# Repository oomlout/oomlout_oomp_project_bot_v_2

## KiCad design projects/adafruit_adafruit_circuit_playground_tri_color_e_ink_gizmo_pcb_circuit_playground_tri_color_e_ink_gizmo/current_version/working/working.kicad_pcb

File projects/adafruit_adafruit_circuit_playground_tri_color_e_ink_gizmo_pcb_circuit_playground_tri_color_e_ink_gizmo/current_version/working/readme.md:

# adafruit_circuit_playground_tri_color_e_ink_gizmo_pcb
 
## summary 
* id: adafruit_adafruit_circuit_playground_tri_color_e_ink_gizmo_pcb_circuit_playground_tri_color_e_ink_gizmo
* user: adafruit
* name: adafruit_circuit_playground_tri_color_e_ink_gizmo_pcb
* board: circuit_playground_tri_color_e_ink_gizmo
* repo: https://github.com/adafruit/Adafruit-Circuit-Playground-Tri-Color-E-Ink-Gizmo-PCB

* src_file_repo_sch: 
* src_file_repo_sch_link: https://github.com/adafruit/Adafruit-Circuit-Playground-Tri-Color-E-Ink-Gizmo-PCB/tree/master/
* full details link: https://github.com/oomlout/oomlout_oomp_project_bot_v_2/tree/main/projects/adafruit_adafruit_circuit_playground_tri_color_e_ink_gizmo_pcb_circuit_playground_tri_color_e_ink_gizmo/current_version/working  

## schematic  
  
[schematic (pdf)](working_schematic.pdf) 

## pcb  

[board (pdf)](working.pdf)  

## working_bom
| Id | Designator | Footprint | Quantity | Designation | Supplier and ref |  | None | 
| --- | --- | --- | --- | --- | --- | --- | --- | 
| 1 | Q5 | SOT23-3 | 1 | IRLML0100 |  |  | [''] | 
| 2 | R13,R12 | 0603-NO | 2 | 100 |  |  | [''] | 
| 3 | U$7 | PCBFEAT-REV-040 | 1 |  |  |  | [''] | 
| 4 | D1,D2 | SOD-323 | 2 | 3.6V |  |  | [''] | 
| 5 | C9,C13,C24,C16 | 0805-NO | 4 | 1uF |  |  | [''] | 
| 6 | TP2,TP4,TP6,TP8,TP7,TP11,TP5,TP13,TP3,TP9,TP10,TP12 | SMT_NUT_3MM | 12 | SEWTAP_SMTNUTM3 |  |  | [''] | 
| 7 | U$2,U$6,U$3 | FIDUCIAL_1MM | 3 | FIDUCIAL_1MM |  |  | [''] | 
| 8 | LEFT0,RIGHT0 | JSTPH3 | 2 | JST PH 3 |  |  | [''] | 
| 9 | C23,C22,C6,C7 | 0805-NO | 4 | 1uF/25V |  |  | [''] | 
| 10 | C8 | 0805-NO | 1 | 10uF/25V |  |  | [''] | 
| 11 | R7 | 0603-NO | 1 | 100K |  |  | [''] | 
| 12 | C10,C5 | 0805-NO | 2 | 1uF/10V |  |  | [''] | 
| 13 | C15,C1,C2 | 0805-NO | 3 | 10uF |  |  | [''] | 
| 14 | VR2 | TRIMPOT_BOURNS_3303W | 1 | 10K trim |  |  | [''] | 
| 15 | C3 | 0805-NO | 1 | 10uF/10V+ |  |  | [''] | 
| 16 | R2,R5 | 0603-NO | 2 | 1K |  |  | [''] | 
| 17 | U$1 | 53398-0271 | 1 | CON_MOLEX_2P |  |  | [''] | 
| 18 | R6 | 0805_10MGAP | 1 | .47ohm |  |  | [''] | 
| 19 | D3,D5,D4 | SOD-123 | 3 | MBR0530 |  |  | [''] | 
| 20 | L1 | INDUCTOR_4X4MM_NR401 | 1 | 10uH |  |  | [''] | 
| 21 | BUSY0 | TP15SQ | 1 | TPTP15SQ |  |  | [''] | 
| 22 | U5 | MSOP8_0.65MM | 1 | PAM8302AASCR |  |  | [''] | 
| 23 | U$4 | EINKGIZMO_BACK | 1 |  |  |  | [''] | 
| 24 | TP18,TP14,TP17,TP16,TP15,TP1 | TESTPOINT_ROUND_1.5MM_NO | 6 |  |  |  | [''] | 
| 25 | U$8 | EINKGIZMO_FRONT | 1 |  |  |  | [''] | 
| 26 | EINK2 | EINK_154IN | 1 | EINK_24PIN_154IN |  |  | [''] | 

## bom_schematic
| Ref | Qnty | Value | Cmp name | Footprint | Description | Vendor | DNP | 
| --- | --- | --- | --- | --- | --- | --- | --- | 
| BUSY0 | 1 | TPTP15SQ | TPTP15SQ | working:TP15SQ |  |  |  | 
| C1, C2, C15 | 3 | 10uF | CAP_CERAMIC0805-NOOUTLINE | working:0805-NO |  |  |  | 
| C3 | 1 | 10uF/10V+ | CAP_CERAMIC0805-NOOUTLINE | working:0805-NO |  |  |  | 
| C5, C10 | 2 | 1uF/10V | CAP_CERAMIC0805-NOOUTLINE | working:0805-NO |  |  |  | 
| C6, C7, C22, C23 | 4 | 1uF/25V | CAP_CERAMIC0805-NOOUTLINE | working:0805-NO |  |  |  | 
| C8 | 1 | 10uF/25V | CAP_CERAMIC0805-NOOUTLINE | working:0805-NO |  |  |  | 
| C9, C13, C16, C24 | 4 | 1uF | CAP_CERAMIC0805-NOOUTLINE | working:0805-NO |  |  |  | 
| D1, D2 | 2 | 3.6V | DIODE-ZENERSOD323 | working:SOD-323 |  |  |  | 
| D3, D4, D5 | 3 | MBR0530 | DIODE-SCHOTTKYSOD-123 | working:SOD-123 |  |  |  | 
| EINK2 | 1 | EINK_24PIN_154IN | EINK_24PIN_154IN | working:EINK_154IN |  |  |  | 
| L1 | 1 | 10uH | INDUCTORNR401 | working:INDUCTOR_4X4MM_NR401 |  |  |  | 
| LEFT0 | 1 | JST PH 3 | CON_JST_PH_3PIN | working:JSTPH3 |  |  |  | 
| Q5 | 1 | IRLML2060TRPBF | IRLML2060TRPBF | working:SOT23-3 |  |  |  | 
| R2, R5 | 2 | 1K | RESISTOR_0603_NOOUT | working:0603-NO |  |  |  | 
| R6 | 1 | .47ohm | RESISTOR0805_10MGAP | working:0805_10MGAP |  |  |  | 
| R7 | 1 | 100K | RESISTOR_0603_NOOUT | working:0603-NO |  |  |  | 
| R12, R13 | 2 | 100 | RESISTOR_0603_NOOUT | working:0603-NO |  |  |  | 
| RIGHT0 | 1 | JST PH 3 | CON_JST_PH_3PIN | working:JSTPH3 |  |  |  | 
| TP1, TP14, TP15, TP16, TP17, TP18 | 6 | TESTPOINTROUND1.5MMNO | TESTPOINTROUND1.5MMNO | working:TESTPOINT_ROUND_1.5MM_NO |  |  |  | 
| TP2, TP3, TP4, TP5, TP6, TP7, TP8, TP9, TP10, TP11, TP12, TP13 | 12 | SEWTAP_SMTNUTM3 | SEWTAP_SMTNUTM3 | working:SMT_NUT_3MM |  |  |  | 
| U5 | 1 | PAM8302AASCR | AUDIOAMP_PAM8302A | working:MSOP8_0.65MM |  |  |  | 
| U$1 | 1 | CON_MOLEX_2P | CON_MOLEX_2P | working:53398-0271 |  |  |  | 
| U$2, U$3, U$6 | 3 | FIDUCIAL_1MM | FIDUCIAL_1MM | working:FIDUCIAL_1MM |  |  |  | 
| VR2 | 1 | 10K trim | TRIMPOT3303W/X | working:TRIMPOT_BOURNS_3303W |  |  |  |

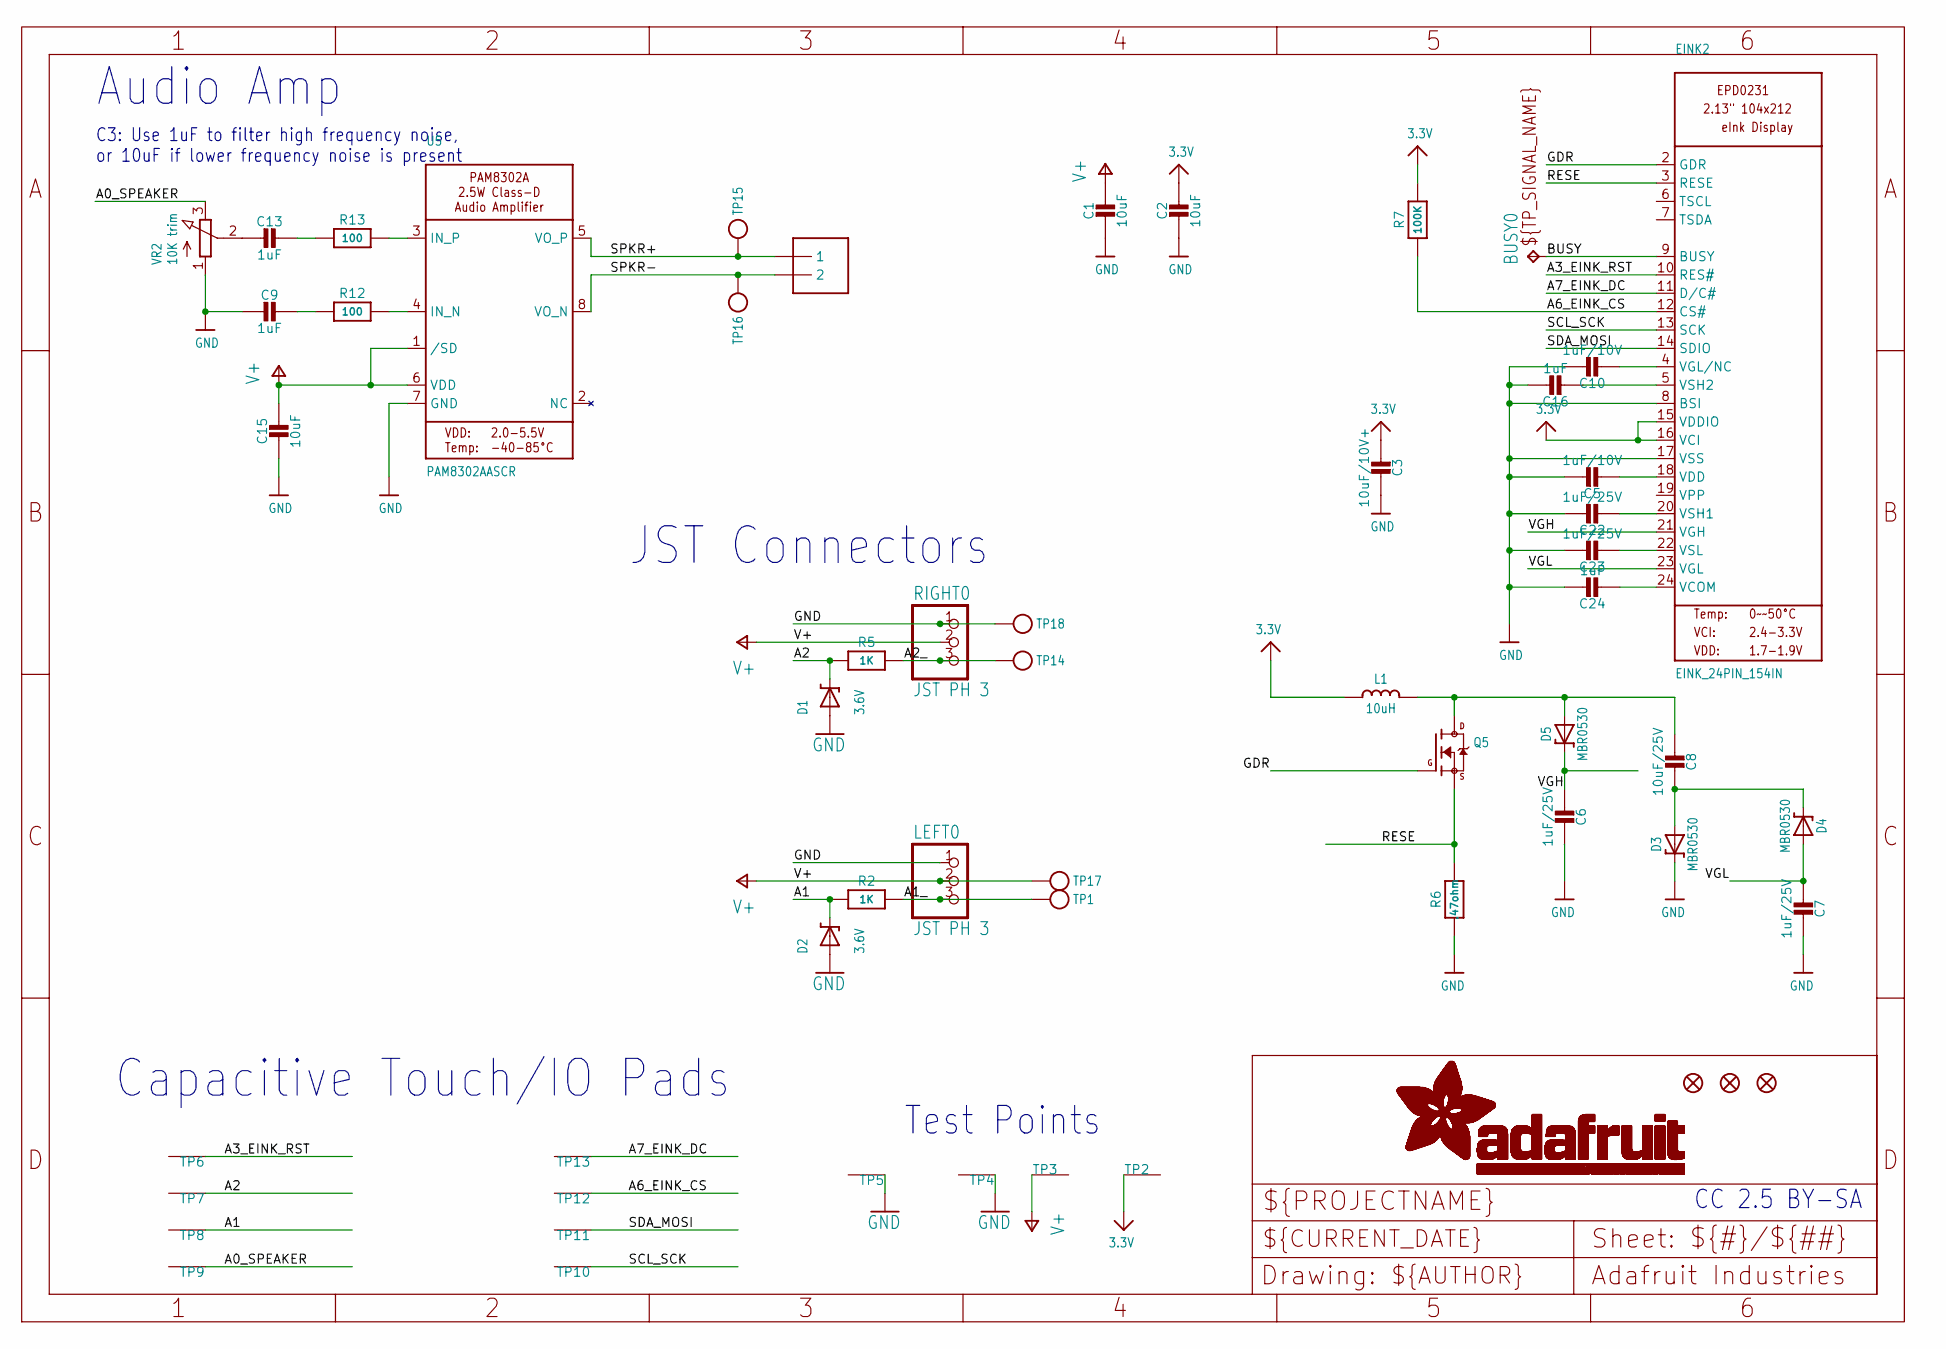
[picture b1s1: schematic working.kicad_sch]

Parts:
BUSY0: TPTP15SQ; TP15SQ
C1, C2, C15: 10uF; 0805-NO
C3: 10uF/10V+; 0805-NO
C5, C10: 1uF/10V; 0805-NO
C6, C7, C22, C23: 1uF/25V; 0805-NO
C8: 10uF/25V; 0805-NO
C9, C13, C16, C24: 1uF; 0805-NO
D1, D2: 3.6V; SOD-323
D3, D4, D5: MBR0530; SOD-123
EINK2: EINK_24PIN_154IN; EINK_154IN
L1: 10uH; INDUCTOR_4X4MM_NR401
LEFT0: JST PH 3; JSTPH3
Q5: IRLML2060TRPBF; SOT23-3
R2, R5: 1K; 0603-NO
R6: .47ohm; 0805_10MGAP
R7: 100K; 0603-NO
R12, R13: 100; 0603-NO
RIGHT0: JST PH 3; JSTPH3
TP1, TP14, TP15, TP16, TP17, TP18: TESTPOINTROUND1.5MMNO; TESTPOINT_ROUND_1.5MM_NO
TP2, TP3, TP4, TP5, TP6, TP7, TP8, TP9, TP10, TP11, TP12, TP13: SEWTAP_SMTNUTM3; SMT_NUT_3MM
U5: PAM8302AASCR; MSOP8_0.65MM
U$1: CON_MOLEX_2P; 53398-0271
U$2, U$3, U$6: FIDUCIAL_1MM
VR2: 10K trim; TRIMPOT_BOURNS_3303W

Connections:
3.3V: C2.1, C3.2, EINK2.15 (VDDIO), EINK2.16 (VCI), L1.P$2 (2), R7.2, TP2.P$1
A0_SPEAKER: TP9.P$1, VR2.3 (E)
A1: D2.C, R2.2, TP8.P$1
A1_: LEFT0.3, R2.1, TP1.P$1
A2: D1.C, R5.2, TP7.P$1
A2_: R5.1, RIGHT0.3, TP14.P$1
A3_EINK_RST: EINK2.10 (RES#), TP6.P$1
A6_EINK_CS: EINK2.12 (CS#), R7.1, TP12.P$1
A7_EINK_DC: EINK2.11 (D/C#), TP13.P$1
BUSY: BUSY0.TP, EINK2.9 (BUSY)
GDR: EINK2.2 (GDR), Q5.1 (G)
GND: C1.2, C2.2, C3.1, C5.1, C6.2, C7.2, C9.2, C10.1, C15.2, C16.1, C22.1, C23.1, C24.1, D1.A, D2.A, D3.C, EINK2.8 (BSI), EINK2.17 (VSS), LEFT0.1, R6.2, RIGHT0.1, TP4.P$1, TP5.P$1, TP18.P$1, U5.7 (GND), VR2.1 (A)
unnamed: C8.2, D3.A, D4.C
unnamed: C8.1, D5.A, L1.P$1 (1), Q5.3 (D)
unnamed: C16.2, EINK2.5 (VSH2)
unnamed: C5.2, EINK2.18 (VDD)
unnamed: C22.2, EINK2.20 (VSH1)
unnamed: C10.2, EINK2.4 (VGL/NC)
unnamed: R12.2, U5.4 (IN_N)
unnamed: R13.2, U5.3 (IN_P)
unnamed: C9.1, R12.1
unnamed: C13.1, R13.1
unnamed: C13.2, VR2.2 (S)
unnamed: C23.2, EINK2.22 (VSL)
unnamed: C24.2, EINK2.24 (VCOM)
RESE: EINK2.3 (RESE), Q5.2 (S), R6.1
SCL_SCK: EINK2.13 (SCK), TP10.P$1
SDA_MOSI: EINK2.14 (SDIO), TP11.P$1
SPKR+: TP15.P$1, U5.5 (VO_P), U$1.1
SPKR-: TP16.P$1, U5.8 (VO_N), U$1.2
V+: C1.1, C15.1, LEFT0.2, RIGHT0.2, TP3.P$1, TP17.P$1, U5.1 (/SD), U5.6 (VDD)
VGH: C6.1, D5.C, EINK2.21 (VGH)
VGL: C7.1, D4.A, EINK2.23 (VGL)

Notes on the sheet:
Audio Amp
Capacitive Touch/IO Pads
CC 2.5 BY-SA
Test Points
JST Connectors
C3: Use 1uF to filter high frequency noise, or 10uF if lower frequency noise is present

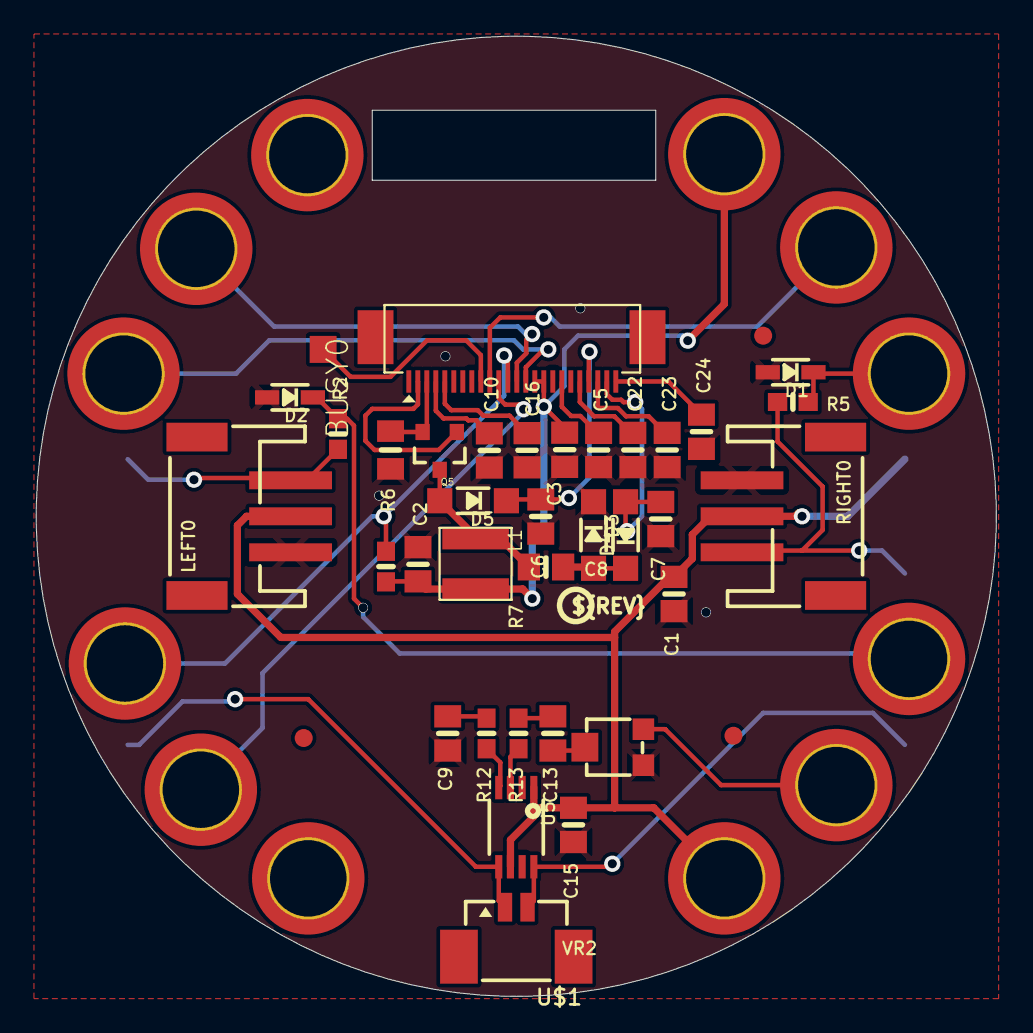
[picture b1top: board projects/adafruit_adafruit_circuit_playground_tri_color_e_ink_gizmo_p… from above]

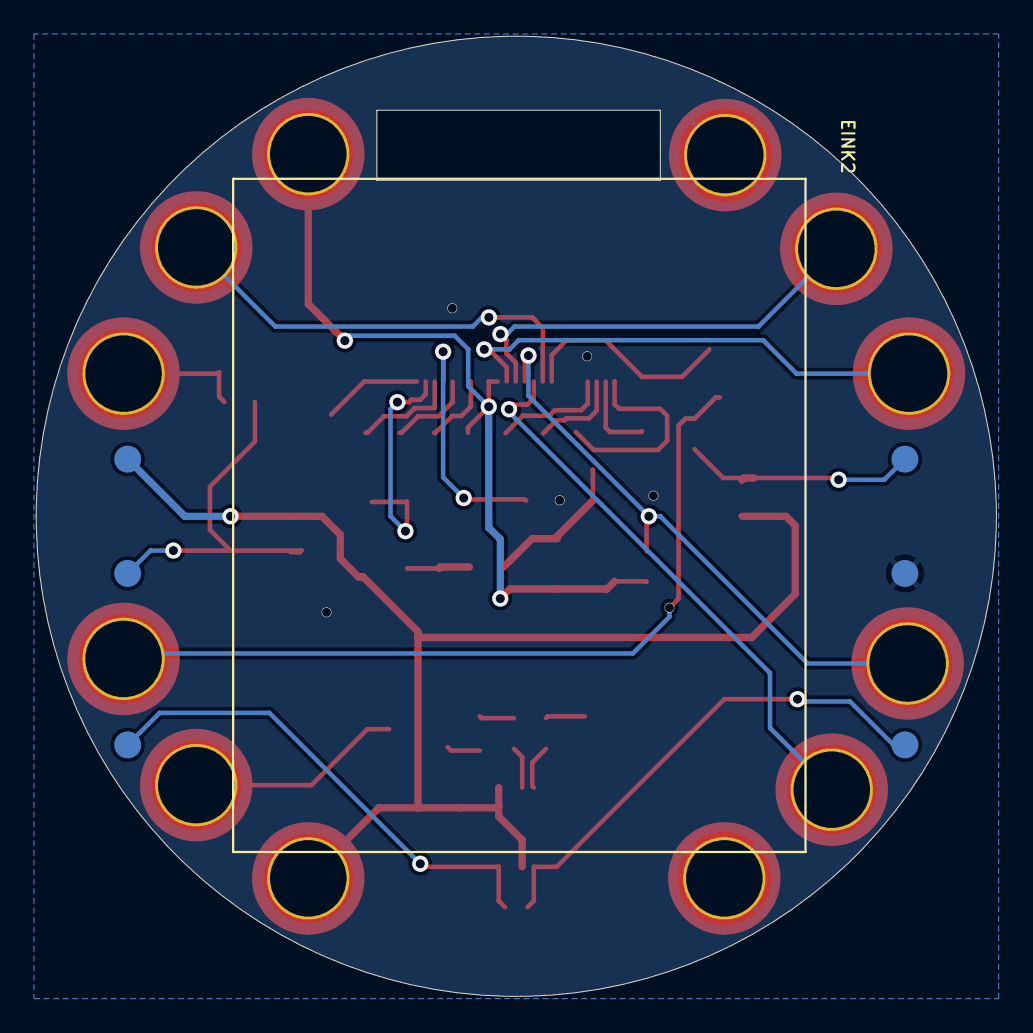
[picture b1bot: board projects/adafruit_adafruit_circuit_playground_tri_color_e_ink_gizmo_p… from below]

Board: 16 copper layers, 53.3 x 53.3 mm, 59 parts (8 on the bottom side), 33 nets.

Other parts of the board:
U$4: EINKGIZMO_BACK
U$7: PCBFEAT-REV-040
U$8: EINKGIZMO_FRONT

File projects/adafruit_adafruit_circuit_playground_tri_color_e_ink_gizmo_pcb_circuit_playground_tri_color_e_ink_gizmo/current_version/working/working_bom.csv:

"Id";"Designator";"Footprint";"Quantity";"Designation";"Supplier and ref";
1;"Q5";"SOT23-3";1;"IRLML0100";;;
2;"R13,R12";"0603-NO";2;"100";;;
3;"U$7";"PCBFEAT-REV-040";1;"";;;
4;"D1,D2";"SOD-323";2;"3.6V";;;
5;"C9,C13,C24,C16";"0805-NO";4;"1uF";;;
6;"TP2,TP4,TP6,TP8,TP7,TP11,TP5,TP13,TP3,TP9,TP10,TP12";"SMT_NUT_3MM";12;"SEWTAP_SMTNUTM3";;;
7;"U$2,U$6,U$3";"FIDUCIAL_1MM";3;"FIDUCIAL_1MM";;;
8;"LEFT0,RIGHT0";"JSTPH3";2;"JST PH 3";;;
9;"C23,C22,C6,C7";"0805-NO";4;"1uF/25V";;;
10;"C8";"0805-NO";1;"10uF/25V";;;
11;"R7";"0603-NO";1;"100K";;;
12;"C10,C5";"0805-NO";2;"1uF/10V";;;
13;"C15,C1,C2";"0805-NO";3;"10uF";;;
14;"VR2";"TRIMPOT_BOURNS_3303W";1;"10K trim";;;
15;"C3";"0805-NO";1;"10uF/10V+";;;
16;"R2,R5";"0603-NO";2;"1K";;;
17;"U$1";"53398-0271";1;"CON_MOLEX_2P";;;
18;"R6";"0805_10MGAP";1;".47ohm";;;
19;"D3,D5,D4";"SOD-123";3;"MBR0530";;;
20;"L1";"INDUCTOR_4X4MM_NR401";1;"10uH";;;
21;"BUSY0";"TP15SQ";1;"TPTP15SQ";;;
22;"U5";"MSOP8_0.65MM";1;"PAM8302AASCR";;;
23;"U$4";"EINKGIZMO_BACK";1;"";;;
24;"TP18,TP14,TP17,TP16,TP15,TP1";"TESTPOINT_ROUND_1.5MM_NO";6;"";;;
25;"U$8";"EINKGIZMO_FRONT";1;"";;;
26;"EINK2";"EINK_154IN";1;"EINK_24PIN_154IN";;;

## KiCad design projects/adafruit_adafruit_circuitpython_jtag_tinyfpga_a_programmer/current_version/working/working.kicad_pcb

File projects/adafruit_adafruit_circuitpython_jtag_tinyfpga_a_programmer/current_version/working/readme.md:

# adafruit_circuitpython_jtag
 
## summary 
* id: adafruit_adafruit_circuitpython_jtag_tinyfpga_a_programmer
* user: adafruit
* name: adafruit_circuitpython_jtag
* board: tinyfpga_a_programmer
* repo: https://github.com/adafruit/Adafruit_CircuitPython_JTAG
* src_file_repo_kicad_pcb: board/TinyFPGA-A-Programmer.kicad_pcb
* src_file_repo_kicad_pcb_link: https://github.com/adafruit/Adafruit_CircuitPython_JTAG/tree/main/board/TinyFPGA-A-Programmer.kicad_pcb

* src_file_repo_sch: board/TinyFPGA-A-Programmer.sch
* src_file_repo_sch_link: https://github.com/adafruit/Adafruit_CircuitPython_JTAG/tree/main/board/TinyFPGA-A-Programmer.sch
* full details link: https://github.com/oomlout/oomlout_oomp_project_bot_v_2/tree/main/projects/adafruit_adafruit_circuitpython_jtag_tinyfpga_a_programmer/current_version/working  

## schematic  
  
[schematic (pdf)](working_schematic.pdf) 

## pcb  

[board (pdf)](working.pdf)  

## working_bom
| Id | Designator | Footprint | Quantity | Designation | Supplier and ref |  | None | 
| --- | --- | --- | --- | --- | --- | --- | --- | 
| 1 | C1,C2,C4 | C_0603 | 3 | 1uF |  |  | [''] | 
| 2 | C3 | C_0603 | 1 | 100nF |  |  | [''] | 
| 3 | J2,J2,J2 | Pin_Header_Straight_1x05_Pitch2.54mm | 3 | JTAG |  |  | [''] | 
| 4 | J3 | Pin_Header_Straight_1x06_Pitch2.54mm | 1 | ICSP |  |  | [''] | 
| 5 | U1 | QFN-16-1EP_4x4mm_Pitch0.65mm | 1 | PIC16F1455-QFN16 |  |  | [''] | 
| 6 | J1 | FCI-Micro-USB | 1 | USB |  |  | [''] | 
| 7 | U2 | SOT23 | 1 | MIC5504-3.3YM5-TR |  |  | [''] | 
| 8 | J2 | Pin_Header_Straight_1x05_Pitch2.54mm_SMD | 1 | JTAG |  |  | [''] | 
| 9 | J4 | Pin_Header_Straight_1x06_Pitch2.54mm | 1 | CONN_01X06 |  |  | [''] | 

## bom_schematic
| Ref | Qnty | Value | Cmp name | Footprint | Description | Vendor | DNP | 
| --- | --- | --- | --- | --- | --- | --- | --- | 
| C1, C2, C4 | 3 | 1uF | C | Capacitors_SMD:C_0603 |  |  |  | 
| C3 | 1 | 100nF | C | Capacitors_SMD:C_0603 |  |  |  | 
| J1 | 1 | USB | USB_OTG | TinyFPGA:FCI-Micro-USB |  |  |  | 
| J2 | 1 | JTAG | CONN_01X05 | Pin_Headers:Pin_Header_Straight_1x05_Pitch2.54mm |  |  |  | 
| J3 | 1 | ICSP | CONN_01X06 | Pin_Headers:Pin_Header_Straight_1x06_Pitch2.54mm |  |  |  | 
| J4 | 1 | CONN_01X06 | CONN_01X06 | Pin_Headers:Pin_Header_Straight_1x06_Pitch2.54mm |  |  |  | 
| TP1, TP2, TP3 | 3 | TEST | TEST | Measurement_Points:Measurement_Point_Round-SMD-Pad_Big |  |  |  | 
| U1 | 1 | PIC16F1455-QFN16 | PIC16F1455-QFN16 | Housings_DFN_QFN:QFN-16-1EP_4x4mm_Pitch0.65mm |  |  |  | 
| U2 | 1 | MIC5504-3.3YM5-TR | MIC5504-3.3YM5-TR | TinyFPGA:SOT23 |  |  |  |

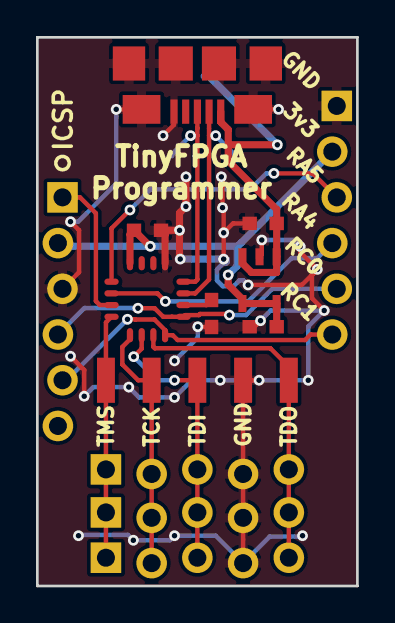
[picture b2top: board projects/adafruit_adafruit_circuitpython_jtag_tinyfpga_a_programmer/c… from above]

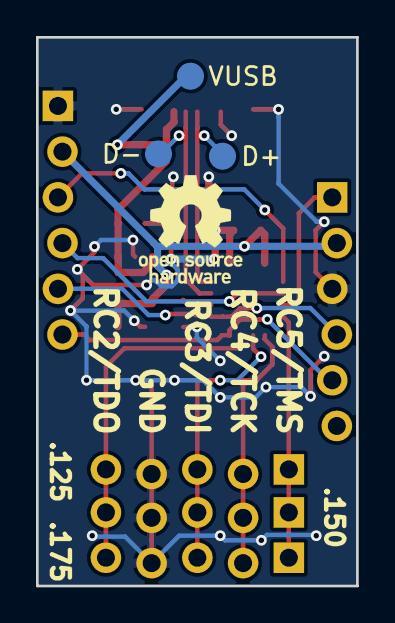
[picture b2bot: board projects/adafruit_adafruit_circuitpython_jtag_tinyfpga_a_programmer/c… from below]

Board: 2 copper layers, 17.8 x 30.5 mm, 16 parts (3 on the bottom side), 15 nets.

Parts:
C1, C2, C4: 1uF; C_0603
C3: 100nF; C_0603
D+: TEST; Measurement_Point_Round-SMD-Pad_Small
D-: TEST; Measurement_Point_Round-SMD-Pad_Small
J1: USB; FCI-Micro-USB
J2, J2#2, J2#3: JTAG; Pin_Header_Straight_1x05_Pitch2.54mm
J2#4: JTAG; Pin_Header_Straight_1x05_Pitch2.54mm_SMD
J3: ICSP; Pin_Header_Straight_1x06_Pitch2.54mm
J4: CONN_01X06; Pin_Header_Straight_1x06_Pitch2.54mm
U1: PIC16F1455-QFN16; QFN-16-1EP_4x4mm_Pitch0.65mm
U2: MIC5504-3.3YM5-TR; SOT23
VUSB: TEST; Measurement_Point_Round-SMD-Pad_Small

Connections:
+3V3: C2.1, C3.1, J3.2, J4.2, U1.16, U2.4, U2.5
+5V: C1.1, J1.1, U2.1, U2.3, VUSB.1
GND: C1.2, C2.2, C3.2, C4.1, J1.5, J1.6, J2.4, J2#2.4, J2#3.4, J2#4.4, J3.3, J4.1, U1.13, U2.2
ICSPCLK: J3.5, J4.6, U1.8
ICSPDAT: J3.4, J4.5, U1.9
unnamed: C4.2, U1.10
unnamed: D-.1, J1.2, U1.11
unnamed: D+.1, J1.3, U1.12
unnamed: J2.1, J2#2.1, J2#3.1, J2#4.1, U1.4
unnamed: J2.2, J2#2.2, J2#3.2, J2#4.2, U1.5
unnamed: J2.3, J2#2.3, J2#3.3, J2#4.3, U1.6
unnamed: J2.5, J2#2.5, J2#3.5, J2#4.5, U1.7
RA4: J4.4, U1.2
RA5: J4.3, U1.1
VPP: J3.1, U1.3

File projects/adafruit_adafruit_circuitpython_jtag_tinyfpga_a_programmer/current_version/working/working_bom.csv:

"Id";"Designator";"Footprint";"Quantity";"Designation";"Supplier and ref";
1;"C1,C2,C4";"C_0603";3;"1uF";;;
2;"C3";"C_0603";1;"100nF";;;
3;"J2,J2,J2";"Pin_Header_Straight_1x05_Pitch2.54mm";3;"JTAG";;;
4;"J3";"Pin_Header_Straight_1x06_Pitch2.54mm";1;"ICSP";;;
5;"U1";"QFN-16-1EP_4x4mm_Pitch0.65mm";1;"PIC16F1455-QFN16";;;
6;"J1";"FCI-Micro-USB";1;"USB";;;
7;"U2";"SOT23";1;"MIC5504-3.3YM5-TR";;;
8;"J2";"Pin_Header_Straight_1x05_Pitch2.54mm_SMD";1;"JTAG";;;
9;"J4";"Pin_Header_Straight_1x06_Pitch2.54mm";1;"CONN_01X06";;;

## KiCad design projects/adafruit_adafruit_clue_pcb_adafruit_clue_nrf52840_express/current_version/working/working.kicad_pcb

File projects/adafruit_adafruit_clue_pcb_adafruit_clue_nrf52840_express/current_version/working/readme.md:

# adafruit_clue_pcb
 
## summary 
* id: adafruit_adafruit_clue_pcb_adafruit_clue_nrf52840_express
* user: adafruit
* name: adafruit_clue_pcb
* board: adafruit_clue_nrf52840_express
* repo: https://github.com/adafruit/Adafruit-CLUE-PCB

* src_file_repo_sch: 
* src_file_repo_sch_link: https://github.com/adafruit/Adafruit-CLUE-PCB/tree/master/
* full details link: https://github.com/oomlout/oomlout_oomp_project_bot_v_2/tree/main/projects/adafruit_adafruit_clue_pcb_adafruit_clue_nrf52840_express/current_version/working  

## schematic  
  
[schematic (pdf)](working_schematic.pdf) 

## pcb  

[board (pdf)](working.pdf)  

## working_bom
| Id | Designator | Footprint | Quantity | Designation | Supplier and ref |  | None | 
| --- | --- | --- | --- | --- | --- | --- | --- | 
| 1 | IC1 | LGA16_3X3MM | 1 | LSM6DS33 |  |  | [''] | 
| 2 | R10,R11 | 0603-NO | 2 | 22 |  |  | [''] | 
| 3 | LED1 | LED3535 | 1 | WS2812B3535 |  |  | [''] | 
| 4 | X1 | 4UCONN_20329_SLIM | 1 | 4u20329 |  |  | [''] | 
| 5 | R8,R7,R9 | 0603-NO | 3 | 1Mohm |  |  | [''] | 
| 6 | D6 | SOD-323 | 1 | 1N4148 |  |  | [''] | 
| 7 | Q1,Q3 | SOT23-WIDE | 2 | BSS138 |  |  | [''] | 
| 8 | IC4 | SPK0415HM4H | 1 | MIC_PDM |  |  | [''] | 
| 9 | R2 | 0603-NO | 1 | 1K |  |  | [''] | 
| 10 | C10,C14,C4,C12,C3,C11 | 0603-NO | 6 | 0.1uF |  |  | [''] | 
| 11 | FID1,FID2,FID4,FID3 | FIDUCIAL_1MM | 4 | FIDUCIAL_1MM |  |  | [''] | 
| 12 | U2 | SOT23-5 | 1 | AP2112(3.3V) |  |  | [''] | 
| 13 | SW1 | EVQ-Q2_SMALLER | 1 | KMR2 |  |  | [''] | 
| 14 | TP2,TP3,TP1 | TESTPOINT_ROUND_1.5MM | 3 |  |  |  | [''] | 
| 15 | D2 | CHIPLED_0603_NOOUTLINE | 1 | RED |  |  | [''] | 
| 16 | D1,D5 | SOD-123 | 2 | MBR120 |  |  | [''] | 
| 17 | C9,C13,C7,C8,C6,C5 | 0805-NO | 6 | 10uF |  |  | [''] | 
| 18 | MDBT1 | MDBT50 | 1 | MDBT50 |  |  | [''] | 
| 19 | R5,R6 | 0603-NO | 2 | 10 |  |  | [''] | 
| 20 | SP1 | BUZZER_SMT_5MM | 1 | SPEAKER_BUZZER5MM |  |  | [''] | 
| 21 | R1,R3 | 0603-NO | 2 | 4.7K |  |  | [''] | 
| 22 | U$10 | PCBFEAT-REV-056 | 1 |  |  |  | [''] | 
| 23 | U1 | SHT3X | 1 | SHT30 |  |  | [''] | 
| 24 | IC2 | SOIC8_150MIL | 1 | GD25Q16 |  |  | [''] | 
| 25 | X3 | JSTPH2 | 1 | JSTPH |  |  | [''] | 
| 26 | U$37 | CLUE_BACK | 1 |  |  |  | [''] | 
| 27 | R4,R12 | 0603-NO | 2 | 10K |  |  | [''] | 
| 28 | L1 | _0805MP | 1 | DNP |  |  | [''] | 
| 29 | CONN1 | JST_SH4 | 1 | STEMMA_I2C_QT |  |  | [''] | 
| 30 | U4 | BMP280 | 1 | BMP280 |  |  | [''] | 
| 31 | IC3 | LGA12_2X2MM | 1 | LIS3MDL |  |  | [''] | 
| 32 | DISPLAY2 | TFT_1.3IN_240X240_24P | 1 | DISP_LCD_ST7789_1.3IN |  |  | [''] | 
| 33 | U3 | APDS-9960 | 1 | APDS-9960 |  |  | [''] | 
| 34 | BTNB0,BTNA0 | 6MMX6MM_TACTILE_SMT | 2 | 6mm |  |  | [''] | 
| 35 | U$52 | CLUE_FRONT | 1 |  |  |  | [''] | 
| 36 | D4,D3 | EVERLIGHT_45-21 | 2 | L130-5780001400001 |  |  | [''] | 
| 37 | MB1 | MICROBIT_EDGE | 1 | MICRO:BIT_EDGE |  |  | [''] | 

## bom_schematic
| Ref | Qnty | Value | Cmp name | Footprint | Description | Vendor | DNP | 
| --- | --- | --- | --- | --- | --- | --- | --- | 
| BTNA0 | 1 | 6mm | SWITCH_TACT_SMT_6MM | working:6MMX6MM_TACTILE_SMT |  |  |  | 
| BTNB0 | 1 | 6mm | SWITCH_TACT_SMT_6MM | working:6MMX6MM_TACTILE_SMT |  |  |  | 
| C3, C4, C10, C11, C12, C14 | 6 | 0.1uF | CAP_CERAMIC0603_NO | working:0603-NO |  |  |  | 
| C5, C6, C7, C8, C9, C13 | 6 | 10uF | CAP_CERAMIC0805-NOOUTLINE | working:0805-NO |  |  |  | 
| CONN1 | 1 | STEMMA_I2C_QT | STEMMA_I2C_QT | working:JST_SH4 |  |  |  | 
| D1, D5 | 2 | MBR120 | DIODE-SCHOTTKYSOD-123 | working:SOD-123 |  |  |  | 
| D2 | 1 | RED | LED0603_NOOUTLINE | working:CHIPLED_0603_NOOUTLINE |  |  |  | 
| D3, D4 | 2 | L130-5780001400001 | LEDEV45-21 | working:EVERLIGHT_45-21 |  |  |  | 
| D6 | 1 | 1N4148 | DIODESOD-323 | working:SOD-323 |  |  |  | 
| DISPLAY2 | 1 | DISP_LCD_ST7789_1.3IN | DISP_LCD_ST7789_1.3IN | working:TFT_1.3IN_240X240_24P |  |  |  | 
| FID1, FID2, FID3, FID4 | 4 | FIDUCIAL_1MM | FIDUCIAL_1MM | working:FIDUCIAL_1MM |  |  |  | 
| IC1 | 1 | LSM6DS33 | LSM6DS33 | working:LGA16_3X3MM |  |  |  | 
| IC2 | 1 | GD25Q16 | SPIFLASH_8PIN | working:SOIC8_150MIL |  |  |  | 
| IC3 | 1 | LIS3MDL | LIS3MDL | working:LGA12_2X2MM |  |  |  | 
| IC4 | 1 | MIC_PDM_SPK0415 | MIC_PDM_SPK0415 | working:SPK0415HM4H |  |  |  | 
| L1 | 1 | DNP | INDUCTOR_0805MP | working:_0805MP |  |  |  | 
| LED1 | 1 | WS2812B3535 | WS2812B3535 | working:LED3535 |  |  |  | 
| MB1 | 1 | MICRO:BIT_EDGE | MICRO{colon}BIT_EDGE | working:MICROBIT_EDGE |  |  |  | 
| MDBT1 | 1 | MDBT50 | MDBT50 | working:MDBT50 |  |  |  | 
| Q1, Q3 | 2 | BSS138 | MOSFET-NWIDE | working:SOT23-WIDE |  |  |  | 
| R1, R3 | 2 | 4.7K | RESISTOR_0603_NOOUT | working:0603-NO |  |  |  | 
| R2 | 1 | 1K | RESISTOR_0603_NOOUT | working:0603-NO |  |  |  | 
| R4, R12 | 2 | 10K | RESISTOR_0603_NOOUT | working:0603-NO |  |  |  | 
| R5, R6 | 2 | 10 | RESISTOR_0603_NOOUT | working:0603-NO |  |  |  | 
| R7, R8, R9 | 3 | 1Mohm | RESISTOR_0603_NOOUT | working:0603-NO |  |  |  | 
| R10, R11 | 2 | 22 | RESISTOR_0603_NOOUT | working:0603-NO |  |  |  | 
| SP1 | 1 | SPEAKER_BUZZER5MM | SPEAKER_BUZZER5MM | working:BUZZER_SMT_5MM |  |  |  | 
| SW1 | 1 | KMR2 | SWITCH_TACT_SMT_EVQQ2_SMALL | working:EVQ-Q2_SMALLER |  |  |  | 
| TP1, TP2, TP3 | 3 | TESTPOINTROUND1.5MM | TESTPOINTROUND1.5MM | working:TESTPOINT_ROUND_1.5MM |  |  |  | 
| U1 | 1 | SHT30 | SHT3X | working:SHT3X |  |  |  | 
| U2 | 1 | AP2112(3.3V) | VREG_SOT23-5 | working:SOT23-5 |  |  |  | 
| U3 | 1 | APDS-9960 | APDS-9960 | working:APDS-9960 |  |  |  | 
| U4 | 1 | BMP280 | BMP280 | working:BMP280 |  |  |  | 
| X1 | 1 | 4u20329 | USB_SLIM | working:4UCONN_20329_SLIM |  |  |  | 
| X3 | 1 | JSTPH | CON_JST_PH_2PIN | working:JSTPH2 |  |  |  |

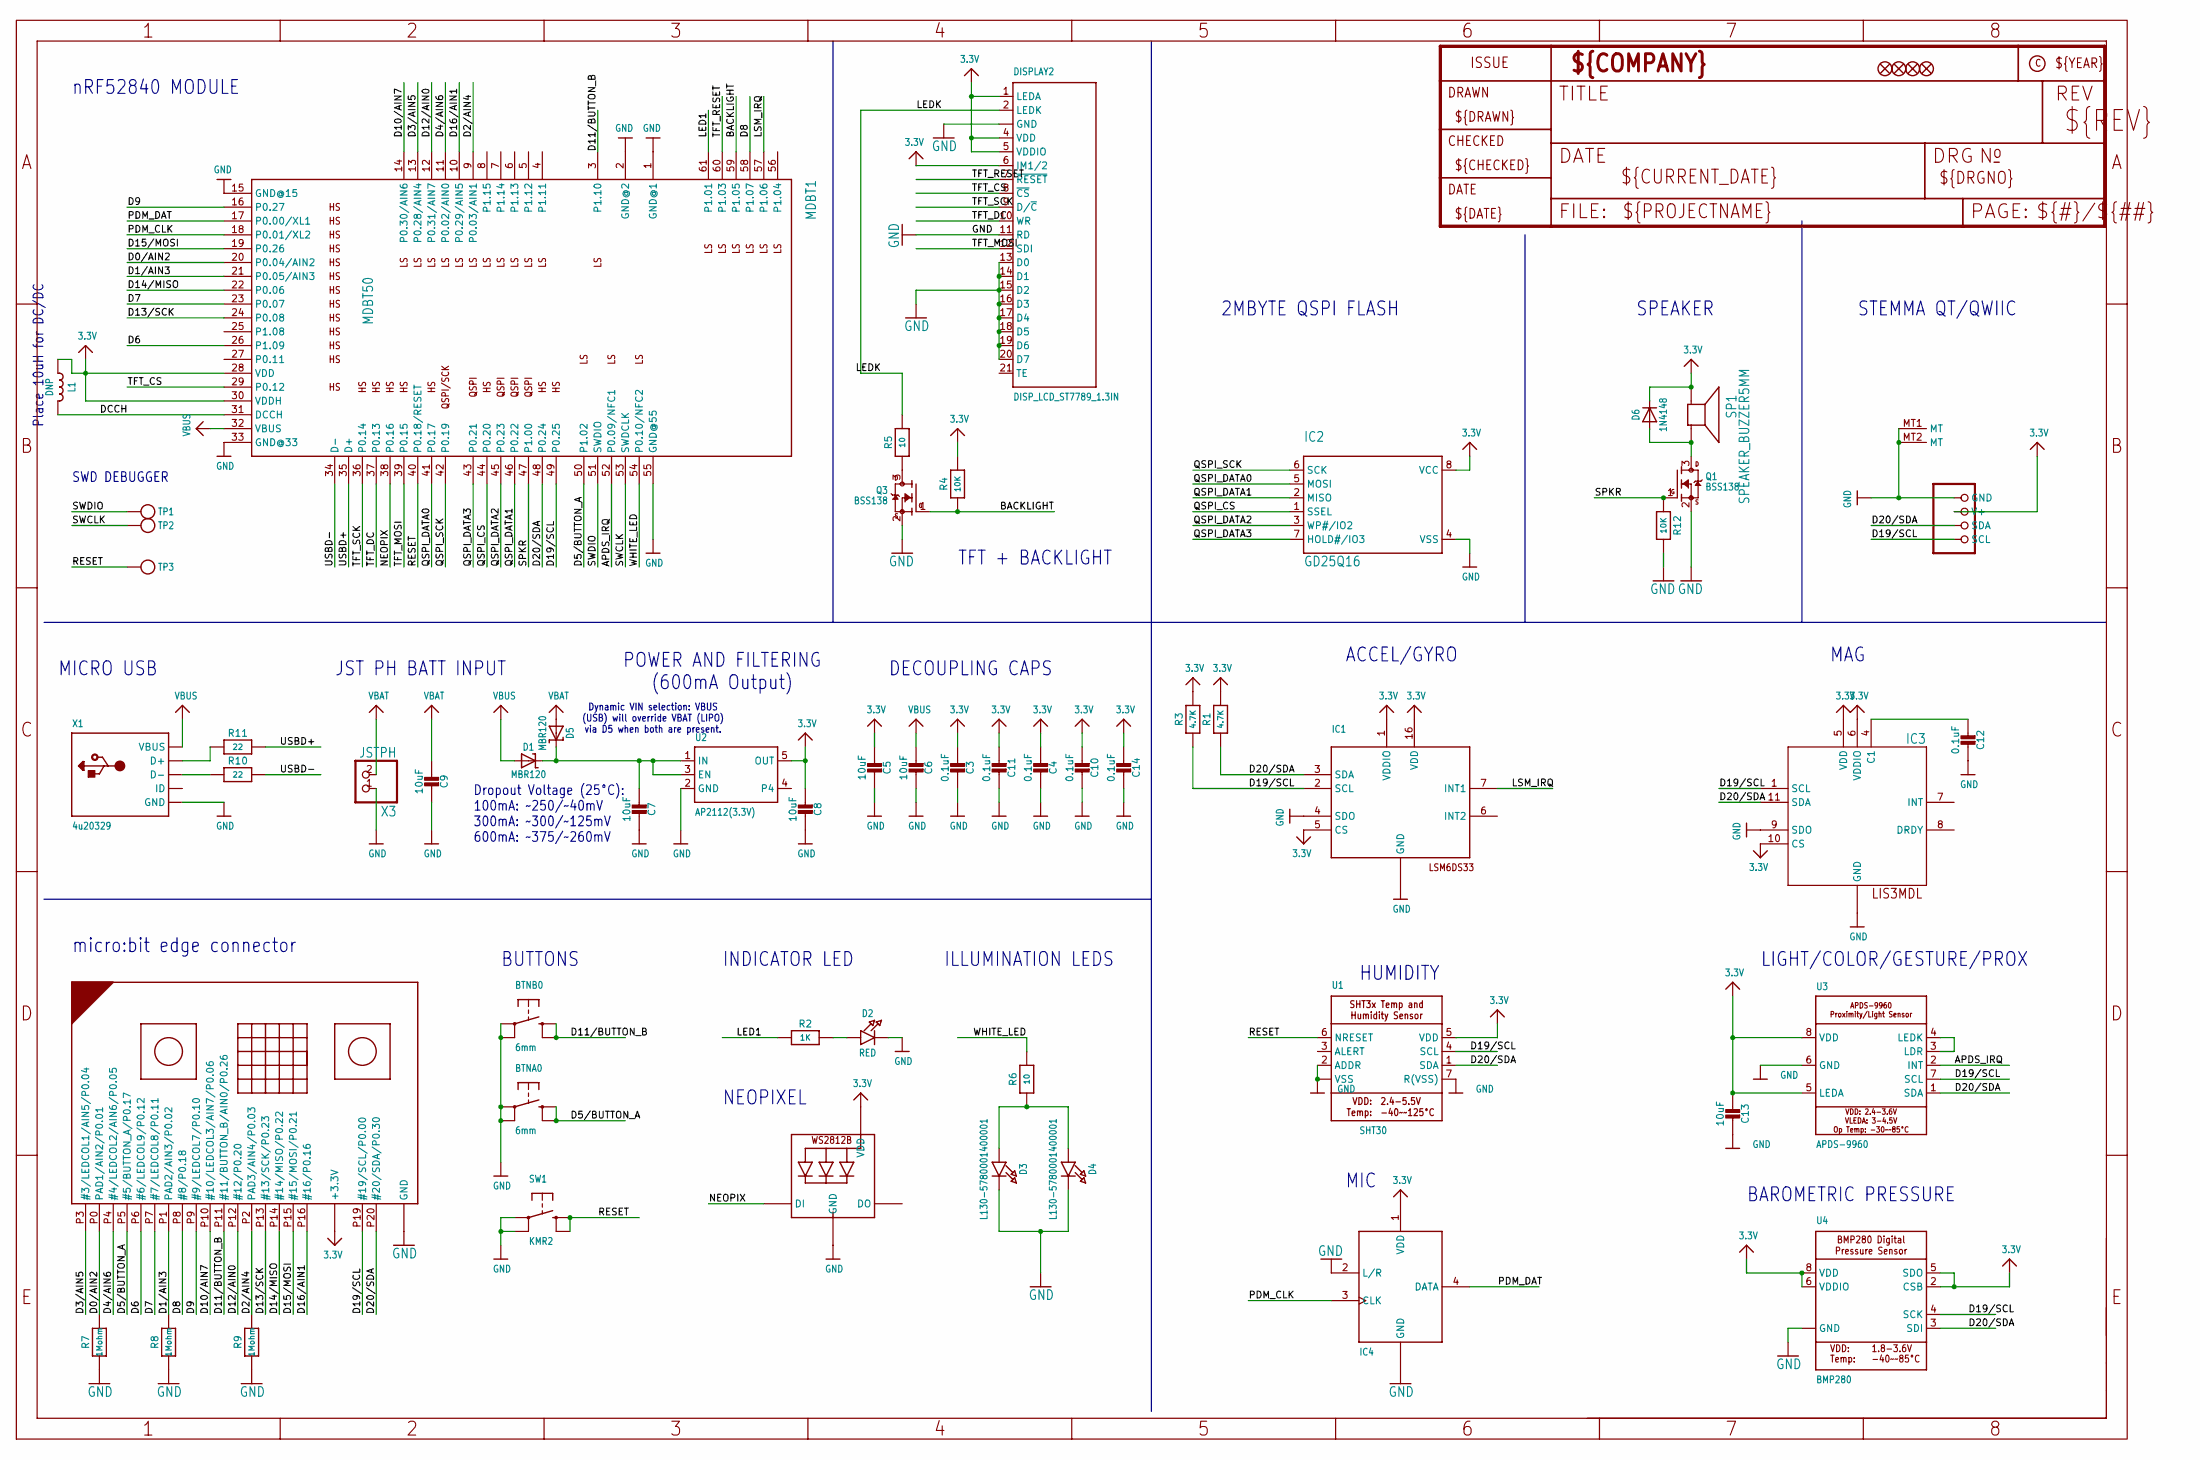
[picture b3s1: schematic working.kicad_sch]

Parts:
BTNA0: 6mm; 6MMX6MM_TACTILE_SMT
BTNB0: 6mm; 6MMX6MM_TACTILE_SMT
C3, C4, C10, C11, C12, C14: 0.1uF; 0603-NO
C5, C6, C7, C8, C9, C13: 10uF; 0805-NO
CONN1: STEMMA_I2C_QT; JST_SH4
D1, D5: MBR120; SOD-123
D2: RED; CHIPLED_0603_NOOUTLINE
D3, D4: L130-5780001400001; EVERLIGHT_45-21
D6: 1N4148; SOD-323
DISPLAY2: DISP_LCD_ST7789_1.3IN; TFT_1.3IN_240X240_24P
FID1, FID2, FID3, FID4: FIDUCIAL_1MM
IC1: LSM6DS33; LGA16_3X3MM
IC2: GD25Q16; SOIC8_150MIL
IC3: LIS3MDL; LGA12_2X2MM
IC4: MIC_PDM_SPK0415; SPK0415HM4H
L1: DNP; _0805MP
LED1: WS2812B3535; LED3535
MB1: MICRO:BIT_EDGE; MICROBIT_EDGE
MDBT1: MDBT50
Q1, Q3: BSS138; SOT23-WIDE
R1, R3: 4.7K; 0603-NO
R2: 1K; 0603-NO
R4, R12: 10K; 0603-NO
R5, R6: 10; 0603-NO
R7, R8, R9: 1Mohm; 0603-NO
R10, R11: 22; 0603-NO
SP1: SPEAKER_BUZZER5MM; BUZZER_SMT_5MM
SW1: KMR2; EVQ-Q2_SMALLER
TP1, TP2, TP3: TESTPOINTROUND1.5MM; TESTPOINT_ROUND_1.5MM
U1: SHT30; SHT3X
U2: AP2112(3.3V); SOT23-5
U3: APDS-9960
U4: BMP280
X1: 4u20329; 4UCONN_20329_SLIM
X3: JSTPH; JSTPH2

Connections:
3.3V: C3.2, C4.2, C5.2, C8.2, C10.2, C11.2, C13.2, C14.2, CONN1.2 (V+), D6.C, DISPLAY2.1 (LEDA), DISPLAY2.4 (VDD), DISPLAY2.5 (VDDIO), DISPLAY2.6 (IM1/2), IC1.1 (VDDIO), IC1.5 (CS), IC1.16 (VDD), IC2.8 (VCC), IC3.5 (VDD), IC3.6 (VDDIO), IC3.10 (CS), IC4.1 (VDD), L1.1, LED1.2 (VDD), MB1.+3V3 (+3.3V), MB1.+3V3@1 (+3.3V), MB1.+3V3@2 (+3.3V), MDBT1.28 (VDD), MDBT1.30 (VDDH), R1.2, R3.2, R4.2, SP1.+, U1.5 (VDD), U2.5 (OUT), U3.5 (LEDA), U3.8 (VDD), U4.2 (CSB), U4.5 (SDO), U4.6 (VDDIO), U4.8 (VDD)
APDS_IRQ: MDBT1.52 (P0.09/NFC1), U3.2 (INT)
BACKLIGHT: MDBT1.59 (P1.05), Q3.1 (G), R4.1
CAP1: C12.2, IC3.4 (C1)
D0/AIN2: MB1.P0 (PAD1/AIN2/P0.01), MDBT1.20 (P0.04/AIN2), R7.2
D1/AIN3: MB1.P1 (PAD2/AIN3/P0.02), MDBT1.21 (P0.05/AIN3), R8.2
D2/AIN4: MB1.P2 (PAD3/AIN4/P0.03), MDBT1.9 (P0.03/AIN1), R9.2
D3/AIN5: MB1.P3 (#3/LEDCOL1/AIN5/P0.04), MDBT1.13 (P0.28/AIN4)
D4/AIN6: MB1.P4 (#4/LEDCOL2/AIN6/P0.05), MDBT1.11 (P0.02/AIN0)
D5/BUTTON_A: BTNA0.B (S), BTNA0.B' (S1), MB1.P5 (#5/BUTTON_A/P0.17), MDBT1.50 (P1.02)
D6: MB1.P6 (#6/LEDCOL9/P0.12), MDBT1.26 (P1.09)
D7: MB1.P7 (#7/LEDCOL8/P0.11), MDBT1.23 (P0.07)
D8: MB1.P8 (#8/P0.18), MDBT1.58 (P1.07)
D9: MB1.P9 (#9/LEDCOL7/P0.10), MDBT1.16 (P0.27)
D10/AIN7: MB1.P10 (#10/LEDCOL3/AIN7/P0.06), MDBT1.14 (P0.30/AIN6)
D11/BUTTON_B: BTNB0.B (S), BTNB0.B' (S1), MB1.P11 (#11/BUTTON_B/AIN0/P0.26), MDBT1.3 (P1.10)
D12/AIN0: MB1.P12 (#12/P0.20), MDBT1.12 (P0.31/AIN7)
D13/SCK: MB1.P13 (#13/SCK/P0.23), MDBT1.24 (P0.08)
D14/MISO: MB1.P14 (#14/MISO/P0.22), MDBT1.22 (P0.06)
D15/MOSI: MB1.P15 (#15/MOSI/P0.21), MDBT1.19 (P0.26)
D16/AIN1: MB1.P16 (#16/P0.16), MDBT1.10 (P0.29/AIN5)
D19/SCL: CONN1.4 (SCL), IC1.2 (SCL), IC3.1 (SCL), MB1.P19 (#19/SCL/P0.00), MDBT1.49 (P0.25), R3.1, U1.4 (SCL), U3.7 (SCL), U4.4 (SCK)
D20/SDA: CONN1.3 (SDA), IC1.3 (SDA), IC3.11 (SDA), MB1.P20 (#20/SDA/P0.30), MDBT1.48 (P0.24), R1.1, U1.1 (SDA), U3.1 (SDA), U4.3 (SDI)
D+: R11.1, X1.D+
D-: R10.1, X1.D-
DCCH: L1.2, MDBT1.31 (DCCH)
GND: BTNA0.A, BTNA0.A' (P1), BTNB0.A, BTNB0.A' (P1), C3.1, C4.1, C5.1, C6.1, C7.1, C8.1, C9.1, C10.1, C11.1, C12.1, C13.1, C14.1, CONN1.1 (GND), CONN1.MT1 (MT), CONN1.MT2 (MT), D2.C, D3.K (C), D4.K (C), DISPLAY2.3 (GND), DISPLAY2.11 (RD), DISPLAY2.13 (D0), DISPLAY2.14 (D1), DISPLAY2.15 (D2), DISPLAY2.16 (D3), DISPLAY2.17 (D4), DISPLAY2.18 (D5), DISPLAY2.19 (D6), DISPLAY2.20 (D7), DISPLAY2.23 (GND), DISPLAY2.24 (GND), IC1.4 (SDO), IC1.8 (GND), IC1.9 (GND), IC1.10 (GND), IC1.11 (GND), IC1.12 (GND), IC1.13 (GND), IC1.15 (GND), IC2.4 (VSS), IC3.2 (GND), IC3.3 (GND), IC3.9 (SDO), IC3.12 (GND), IC4.2 (L/R), IC4.5 (GND), IC4.6 (GND), IC4.7 (GND), IC4.8 (GND), LED1.4 (GND), MB1.GND, MB1.GND@1 (GND), MB1.GND@2 (GND), MDBT1.1 (GND@1), MDBT1.2 (GND@2), MDBT1.15 (GND@15), MDBT1.33 (GND@33), MDBT1.55 (GND@55), Q1.2 (S), Q3.2 (S), R7.1, R8.1, R9.1, R12.2, SW1.A, SW1.A' (P1), U1.2 (ADDR), U1.7 (R(VSS)), U1.8 (VSS), U1.THERMAL (VSS), U2.2 (GND), U3.6 (GND), U4.1 (GND), U4.7 (GND), X1.BASE@1 (GND), X1.BASE@2 (GND), X1.GND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
LED1: MDBT1.61 (P1.01), R2.1
LEDK: DISPLAY2.2 (LEDK), R5.2
LSM_IRQ: IC1.7 (INT1), MDBT1.57 (P1.06)
unnamed: Q3.3 (D), R5.1
unnamed: U3.3 (LDR), U3.4 (LEDK)
unnamed: D3.A, D4.A, R6.1
unnamed: D6.A, Q1.3 (D), SP1.-
unnamed: D2.A, R2.2
NEOPIX: LED1.1 (DI), MDBT1.38 (P0.16)
PDM_CLK: IC4.3 (CLK), MDBT1.18 (P0.01/XL2)
PDM_DAT: IC4.4 (DATA), MDBT1.17 (P0.00/XL1)
QSPI_CS: IC2.1 (SSEL), MDBT1.44 (P0.20)
QSPI_DATA0: IC2.5 (MOSI), MDBT1.41 (P0.17)
QSPI_DATA1: IC2.2 (MISO), MDBT1.46 (P0.22)
QSPI_DATA2: IC2.3 (WP#/IO2), MDBT1.45 (P0.23)
QSPI_DATA3: IC2.7 (HOLD#/IO3), MDBT1.43 (P0.21)
QSPI_SCK: IC2.6 (SCK), MDBT1.42 (P0.19)
RESET: MDBT1.40 (P0.18/RESET), SW1.B (S), SW1.B' (S1), TP3.P$1, U1.6 (NRESET)
SPKR: MDBT1.47 (P1.00), Q1.1 (G), R12.1
SWCLK: MDBT1.53 (SWDCLK), TP2.P$1
SWDIO: MDBT1.51 (SWDIO), TP1.P$1
TFT_CS: DISPLAY2.8 (~CS), MDBT1.29 (P0.12)
TFT_DC: DISPLAY2.10 (WR), MDBT1.37 (P0.13)
TFT_MOSI: DISPLAY2.12 (SDI), MDBT1.39 (P0.15)
TFT_RESET: DISPLAY2.7 (~RESET), MDBT1.60 (P1.03)
TFT_SCK: DISPLAY2.9 (D/~C), MDBT1.36 (P0.14)
USBD+: MDBT1.35 (D+), R11.2
USBD-: MDBT1.34 (D-), R10.2
VBAT: C9.2, D5.A, X3.2
VBUS: C6.2, D1.A, MDBT1.32 (VBUS), X1.VBUS
VHI: C7.2, D1.C, D5.C, U2.1 (IN), U2.3 (EN)
WHITE_LED: MDBT1.54 (P0.10/NFC2), R6.2

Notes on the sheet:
MAG
micro:bit edge connector
Place 10uH for DC/DC
JST PH BATT INPUT
HUMIDITY
Dropout Voltage (25°C): 100mA: ~250/~40mV 300mA: ~300/~125mV 600mA: ~375/~260mV
DECOUPLING CAPS
SWD DEBUGGER
Dynamic VIN selection: VBUS (USB) will override VBAT (LIPO) via D5 when both are present.
MIC
INDICATOR LED
ACCEL/GYRO
ILLUMINATION LEDS
TFT + BACKLIGHT
POWER AND FILTERING (600mA Output)
SPEAKER
LIGHT/COLOR/GESTURE/PROX
BAROMETRIC PRESSURE
MICRO USB
nRF52840 MODULE
NEOPIXEL
STEMMA QT/QWIIC
2MBYTE QSPI FLASH
BUTTONS

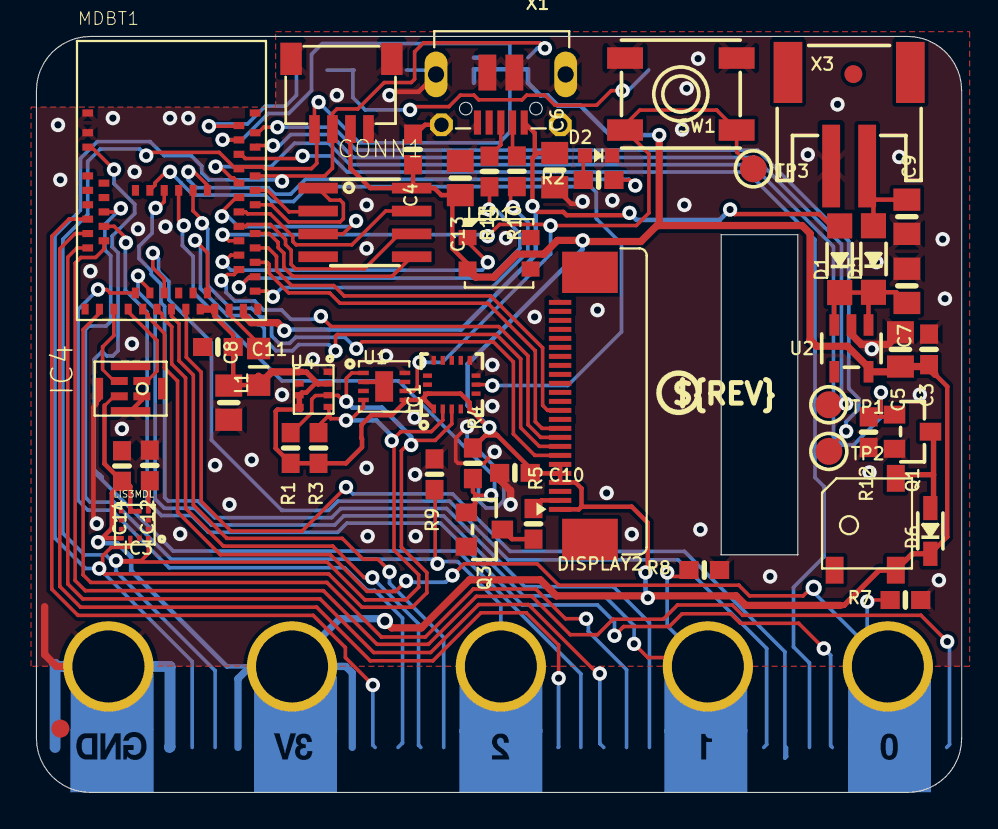
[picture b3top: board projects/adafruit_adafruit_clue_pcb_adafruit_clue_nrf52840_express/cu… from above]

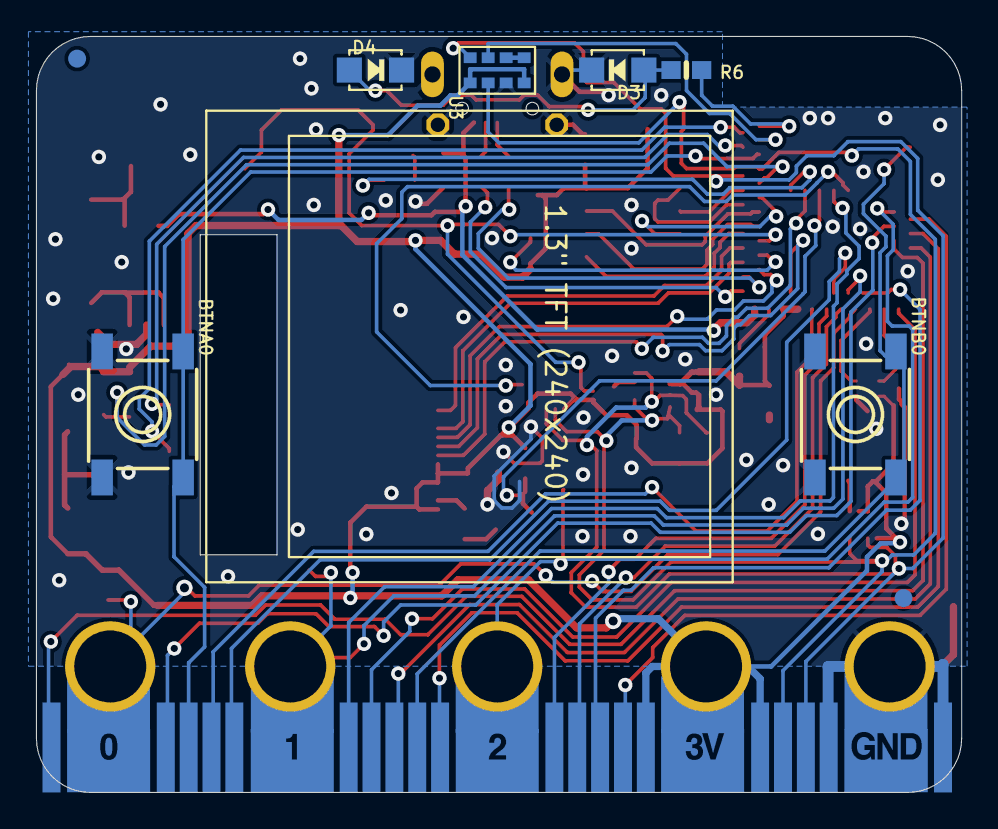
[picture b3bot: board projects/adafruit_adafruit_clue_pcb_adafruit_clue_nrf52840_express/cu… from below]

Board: 2 copper layers, 51.4 x 42.0 mm, 62 parts (10 on the bottom side), 59 nets.

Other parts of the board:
U$10: PCBFEAT-REV-056
U$37: CLUE_BACK
U$52: CLUE_FRONT

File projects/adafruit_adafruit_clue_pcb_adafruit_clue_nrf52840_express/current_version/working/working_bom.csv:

"Id";"Designator";"Footprint";"Quantity";"Designation";"Supplier and ref";
1;"IC1";"LGA16_3X3MM";1;"LSM6DS33";;;
2;"R10,R11";"0603-NO";2;"22";;;
3;"LED1";"LED3535";1;"WS2812B3535";;;
4;"X1";"4UCONN_20329_SLIM";1;"4u20329";;;
5;"R8,R7,R9";"0603-NO";3;"1Mohm";;;
6;"D6";"SOD-323";1;"1N4148";;;
7;"Q1,Q3";"SOT23-WIDE";2;"BSS138";;;
8;"IC4";"SPK0415HM4H";1;"MIC_PDM";;;
9;"R2";"0603-NO";1;"1K";;;
10;"C10,C14,C4,C12,C3,C11";"0603-NO";6;"0.1uF";;;
11;"FID1,FID2,FID4,FID3";"FIDUCIAL_1MM";4;"FIDUCIAL_1MM";;;
12;"U2";"SOT23-5";1;"AP2112(3.3V)";;;
13;"SW1";"EVQ-Q2_SMALLER";1;"KMR2";;;
14;"TP2,TP3,TP1";"TESTPOINT_ROUND_1.5MM";3;"";;;
15;"D2";"CHIPLED_0603_NOOUTLINE";1;"RED";;;
16;"D1,D5";"SOD-123";2;"MBR120";;;
17;"C9,C13,C7,C8,C6,C5";"0805-NO";6;"10uF";;;
18;"MDBT1";"MDBT50";1;"MDBT50";;;
19;"R5,R6";"0603-NO";2;"10";;;
20;"SP1";"BUZZER_SMT_5MM";1;"SPEAKER_BUZZER5MM";;;
21;"R1,R3";"0603-NO";2;"4.7K";;;
22;"U$10";"PCBFEAT-REV-056";1;"";;;
23;"U1";"SHT3X";1;"SHT30";;;
24;"IC2";"SOIC8_150MIL";1;"GD25Q16";;;
25;"X3";"JSTPH2";1;"JSTPH";;;
26;"U$37";"CLUE_BACK";1;"";;;
27;"R4,R12";"0603-NO";2;"10K";;;
28;"L1";"_0805MP";1;"DNP";;;
29;"CONN1";"JST_SH4";1;"STEMMA_I2C_QT";;;
30;"U4";"BMP280";1;"BMP280";;;
31;"IC3";"LGA12_2X2MM";1;"LIS3MDL";;;
32;"DISPLAY2";"TFT_1.3IN_240X240_24P";1;"DISP_LCD_ST7789_1.3IN";;;
33;"U3";"APDS-9960";1;"APDS-9960";;;
34;"BTNB0,BTNA0";"6MMX6MM_TACTILE_SMT";2;"6mm";;;
35;"U$52";"CLUE_FRONT";1;"";;;
36;"D4,D3";"EVERLIGHT_45-21";2;"L130-5780001400001";;;
37;"MB1";"MICROBIT_EDGE";1;"MICRO:BIT_EDGE";;;
